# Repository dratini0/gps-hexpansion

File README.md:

# GPS hexpansion

I came into posession of 95 surplous Ublox MAX-M10S GPS modules.
I just had to put some of them down on a hexpansion.

## Acknowledgements

Uses the [hexpansion template from EMF](https://github.com/emfcamp/badge-2024-hardware/tree/main/hexpansion)

I have attempted to maintain some pinout compatibility with [TechCabin's design](https://github.com/TechCabin/EMFBadge-Hexpansions-GPS), but it uses a very different chip.
Sorry for stepping on your toes!

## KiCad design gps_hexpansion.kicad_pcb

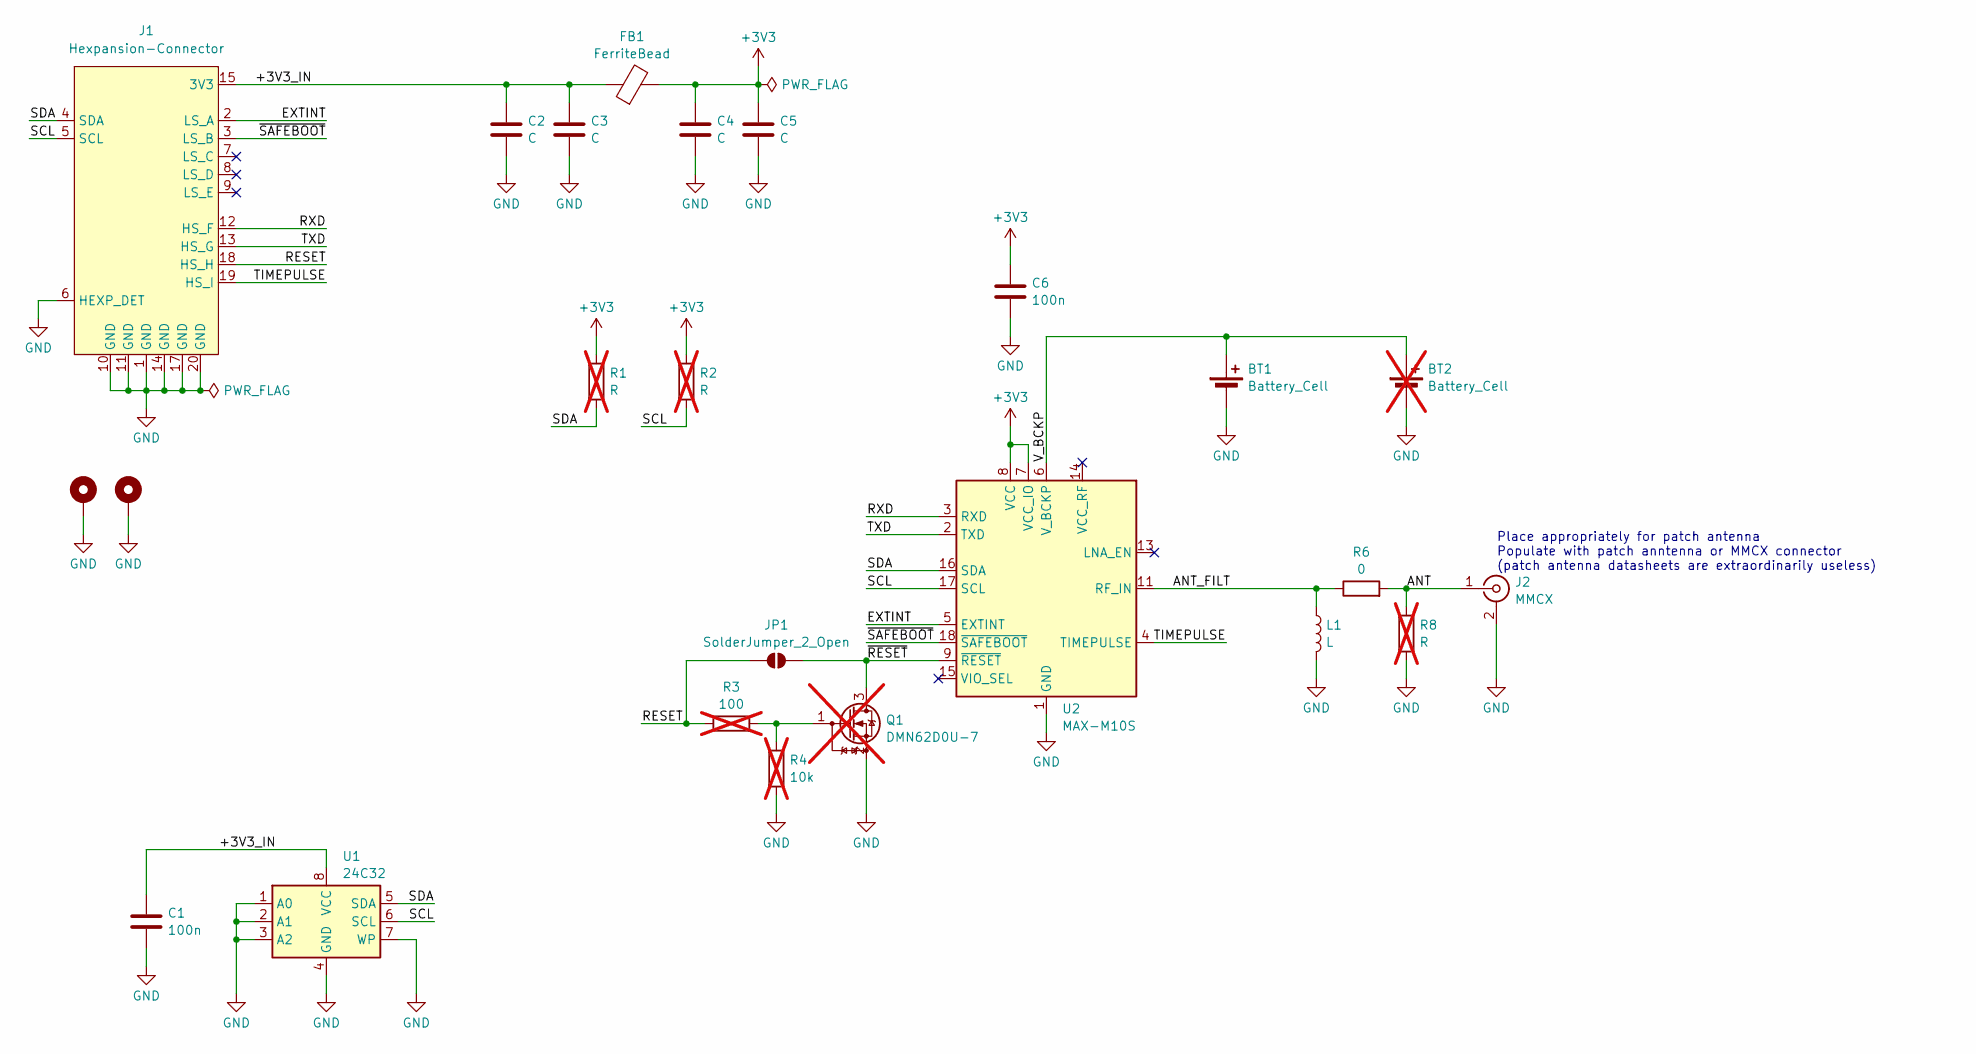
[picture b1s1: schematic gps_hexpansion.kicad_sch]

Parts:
BT1: Battery_Cell; card_edge_CR2032
BT2: Battery_Cell; BatteryHolder_Keystone_3000_1x12mm; not fitted
C1, C6: 100n; C_0805_2012Metric_Pad1.18x1.45mm_HandSolder
C2, C3, C4, C5: C; C_0805_2012Metric_Pad1.18x1.45mm_HandSolder
FB1: FerriteBead; L_0805_2012Metric_Pad1.05x1.20mm_HandSolder
H1, H2: MountingHole_Pad; MountingHole_2.2mm_M2_Pad_Via
J1: Hexpansion-Connector; hexpansion-edge-connector
J2: MMCX; MMCX_Molex_73415-1471_Vertical
JP1: SolderJumper_2_Open; SolderJumper-2_P1.3mm_Open_TrianglePad1.0x1.5mm
L1: L; L_0603_1608Metric
Q1: DMN62D0U-7; SOT-23; LCSC C151421; not fitted
R1, R2: R; R_0805_2012Metric_Pad1.20x1.40mm_HandSolder; not fitted
R3: 100; R_0805_2012Metric_Pad1.20x1.40mm_HandSolder; not fitted
R4: 10k; R_0805_2012Metric_Pad1.20x1.40mm_HandSolder; not fitted
R6: 0; R_0603_1608Metric
R8: R; R_0603_1608Metric; not fitted
U1: 24C32; SOIC-8_3.9x4.9mm_P1.27mm
U2: MAX-M10S; ublox_MAX

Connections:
+3V3: C4.1, C5.1, C6.1, FB1.2, R1.1, R2.1, U2.7 (VCC_IO), U2.8 (VCC)
/+3V3_IN: C1.1, C2.1, C3.1, FB1.1, J1.15 (3V3), J1.16 (3V3), U1.8 (VCC)
/ANT: J2.1 (In), R6.2, R8.2
/ANT_FILT: L1.1, R6.1, U2.11 (RF_IN)
/EXTINT: J1.2 (LS_A), U2.5 (EXTINT)
/RESET: J1.18 (HS_H), JP1.1 (A), R3.1
/RXD: J1.12 (HS_F), U2.3 (RXD)
/SCL: J1.5 (SCL), R2.2, U1.6 (SCL), U2.17 (SCL)
/SDA: J1.4 (SDA), R1.2, U1.5 (SDA), U2.16 (SDA)
/TIMEPULSE: J1.19 (HS_I), U2.4 (TIMEPULSE)
/TXD: J1.13 (HS_G), U2.2 (TXD)
/V_BCKP: BT1.1 (+), BT2.1 (+), U2.6 (V_BCKP)
/~RESET: JP1.2 (B), Q1.3 (D), U2.9 (~RESET)
/~SAFEBOOT: J1.3 (LS_B), U2.18 (~SAFEBOOT)
GND: BT1.2 (-), BT2.2 (-), C1.2, C2.2, C3.2, C4.2, C5.2, C6.2, H1.1, H2.1, J1.1 (GND), J1.6 (HEXP_DET), J1.10 (GND), J1.11 (GND), J1.14 (GND), J1.17 (GND), J1.20 (GND), J2.2 (Ext), L1.2, Q1.2 (S), R4.2, R8.1, U1.1 (A0), U1.2 (A1), U1.3 (A2), U1.4 (GND), U1.7 (WP), U2.1 (GND), U2.10 (GND), U2.12 (GND)
unnamed: Q1.1 (G), R3.2, R4.1

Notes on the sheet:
Place appropriately for patch antenna Populate with patch anntenna or MMCX connector (patch antenna datasheets are extraordinarily useless)

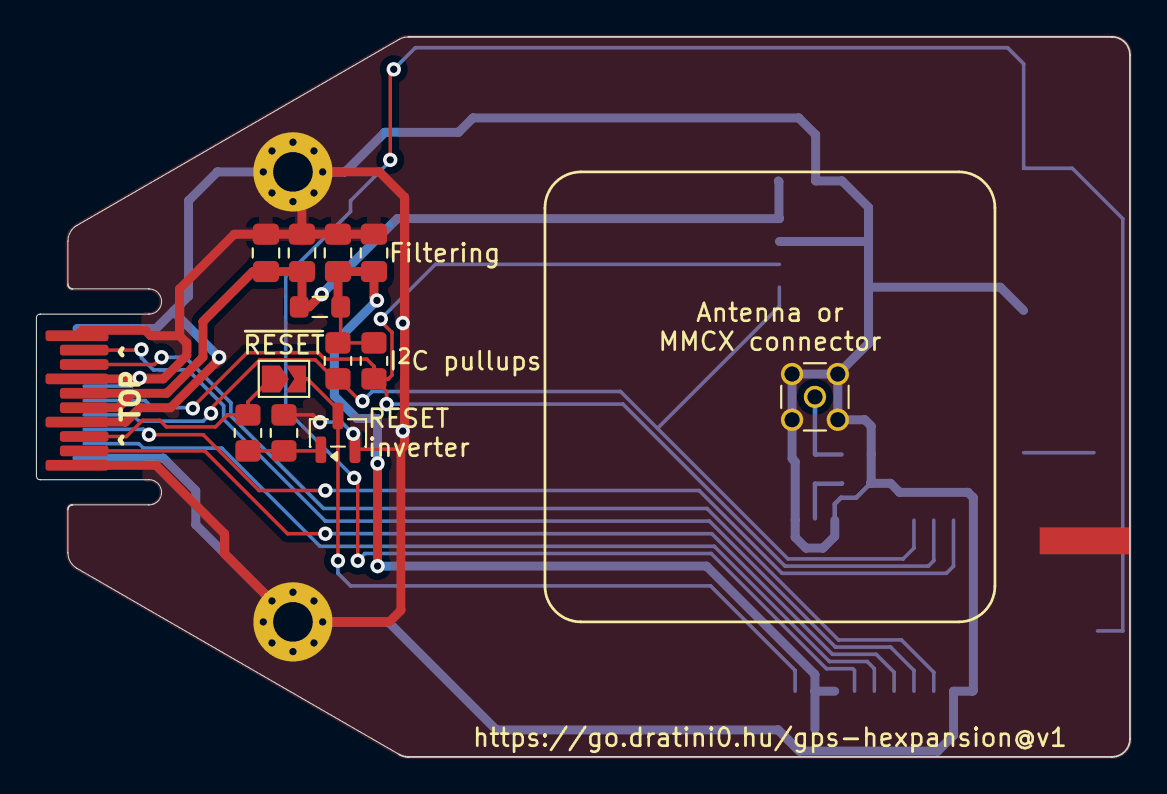
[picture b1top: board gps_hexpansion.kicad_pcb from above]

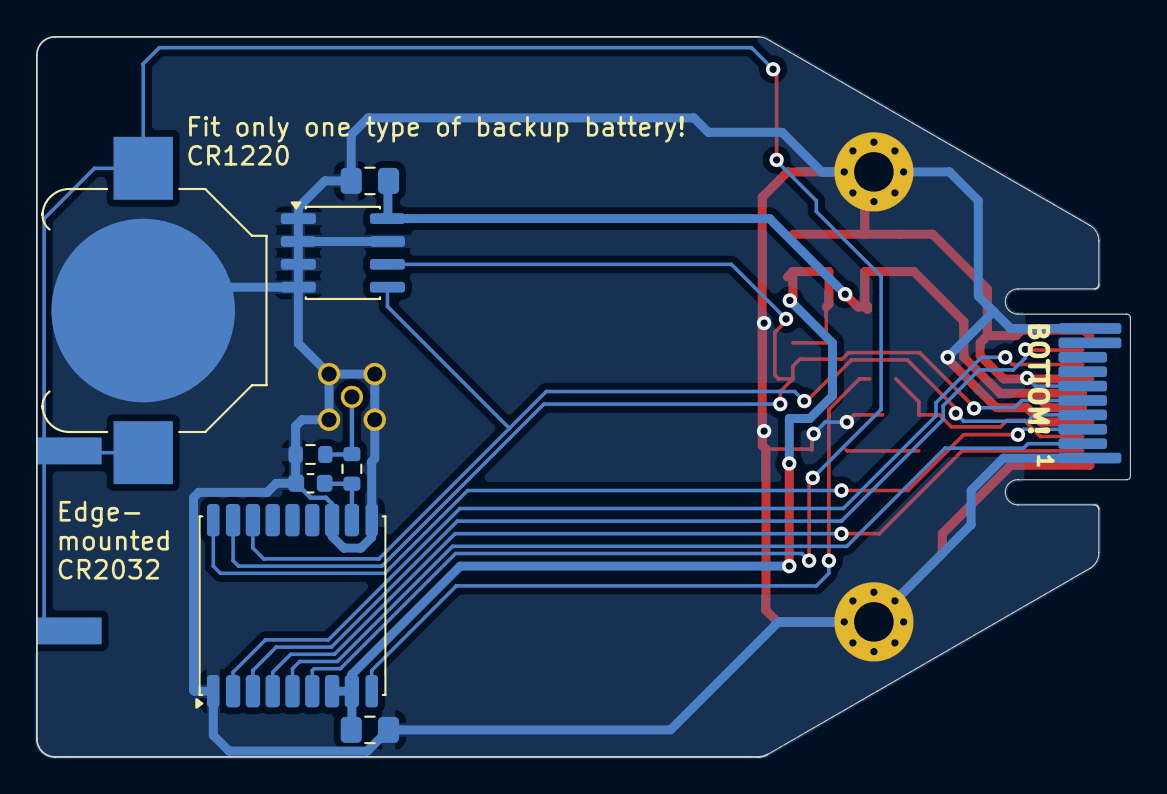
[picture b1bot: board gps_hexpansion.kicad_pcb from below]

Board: 2 copper layers, 60.8 x 40.0 mm, 24 parts (9 on the bottom side), 16 nets.
